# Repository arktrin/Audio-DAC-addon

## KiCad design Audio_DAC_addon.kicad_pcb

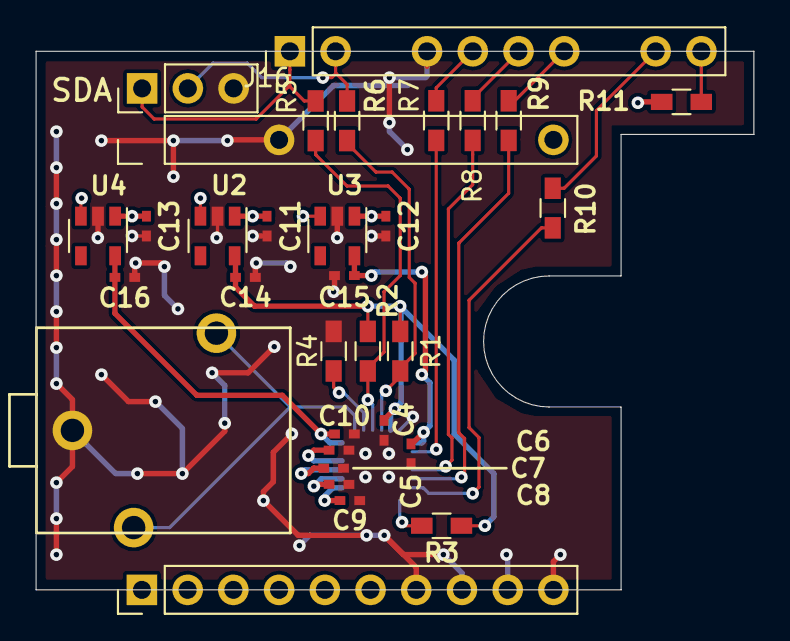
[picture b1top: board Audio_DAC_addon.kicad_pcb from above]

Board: 2 copper layers, 39.9 x 29.9 mm, 33 parts (1 on the bottom side), 25 nets.

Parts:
C4, C5, C7, C8, C9, C10, C11, C12, C13, C14, C15, C16: 1uF; C_0402_NoSilk
C6: 2.2uF; C_0402_NoSilk
J1: Audio-Jack-3; AUB-11_audio-jack
J2: Conn_01x03; Pin_Header_Straight_1x03_Pitch2.54mm
J16, J25, J28: Conn_01x10; Pin_Header_Straight_1x10_Pitch2.54mm
R1, R2, R3, R4, R5, R6, R7, R8, R9, R10, R11: R; R_0603_HandSoldering
U1: MAX9860; QFN-24-1EP_4x4mm_Pitch0.5mm
U2: TLV70033DCKR; SOT-23-5
U3, U4: TLV70018DDCR; SOT-23-5

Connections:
/AVDD: C10.1, C16.1, U1.6, U4.5
/BCLK: R10.1, U1.18
/DVDD: C5.1, C15.1, U1.13, U3.5
/DVDDIO_3V3: C4.1, C14.1, R1.2, R2.1, R3.1, U1.11, U2.5
/FPGA_AE15: J16.9, R10.2
/FPGA_AF17: J16.10, R11.2
/FPGA_AG11: J2.1, J16.1, R5.1
/FPGA_AG16: J16.7, R9.2
/FPGA_AH9: J2.2, J16.2, R6.1
/FPGA_AH11: J16.6, R8.2
/FPGA_AH12: J16.5, R7.2
/IRQ: R3.2, U1.19
/LRCLK: R9.1, U1.17
/MCLK: R7.1, U1.14
/MICBIAS: C9.1, U1.1
/OUTN: R4.1, U1.8
/OUTP: J1.1, J1.2, U1.7
/PREG: C7.1, U1.3
/REF: C6.1, U1.4
/REG: C8.1, U1.2
/SCL: R1.1, R6.2, U1.10
/SDA: R2.2, R5.2, U1.9
/SDIN: R8.1, U1.16
GND: C4.2, C5.2, C6.2, C7.2, C8.2, C9.2, C10.2, C11.2, C12.2, C13.2, C14.2, C15.2, C16.2, J1.3, J2.3, J16.4, J25.4, J28.7, J28.8, J28.9, J28.10, R4.2, U1.5, U1.12, U1.20, U1.21, U1.22, U1.23, U1.24, U1.25, U2.2, U3.2, U4.2
VCC: C11.1, C12.1, C13.1, J25.10, U2.1, U2.3, U3.1, U3.3, U4.1, U4.3

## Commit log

2018-03-11 (pre) initial commit
2018-03-11 change title
2018-03-16 real initial commit
2018-03-17 add LDOs + pcb progress
2018-03-18 pcb and circuit diagram are almost done
2018-03-19 add silkscreen
2018-03-19 generate gerber + lots of bug fix
